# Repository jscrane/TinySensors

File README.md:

View this project on [CADLAB.io](https://cadlab.io/project/1612). 

TinySensors
===========
See [blog articles](http://programmablehardware.blogspot.ie/search/label/tinysensor).

* hub: lightweight Raspberry Pi server-side for TinySensor
* sensing: Database viewer
* eagle: TinySensor Eagle project

Software
========
* Arduino
  - IDE version [1.8.9](http://arduino.cc/en/Main/Software) or [uC-Makefile](https://github.com/jscrane/uC-Makefile)
  - [ATtiny core](https://github.com/SpenceKonde/ATTinyCore)
  - [nRF24](https://github.com/nRF24/RF24) library
  - [DHT22](https://github.com/jscrane/DHT22) library, slimmed-down for ATtiny

* Raspberry-Pi
  - Tested on Raspberry Pi 2, Pi 3 Model B and Pi Zero-W
  - [nRF24](https://github.com/nRF24/RF24) library
  - [BCM2835](http://www.airspayce.com/mikem/bcm2835) library
  - libmosquitto-dev
  - lcdproc

* Viewer
  - [Leiningen](http://leiningen.org) v2.0, or
  - [IntelliJ](http://www.jetbrains.com/idea) with the
[Cursive](https://cursiveclojure.com) plugin

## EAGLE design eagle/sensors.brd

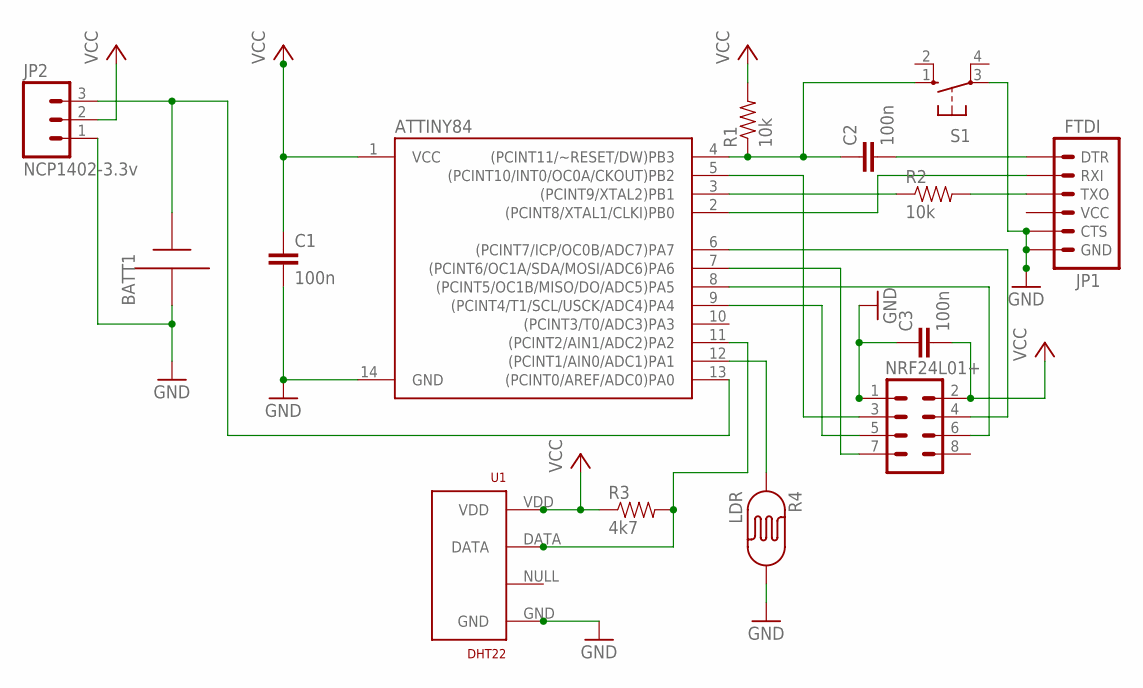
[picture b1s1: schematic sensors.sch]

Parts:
ATTINY84: ATTINY84ATTINY84-20PU; DIL14
BATT1: AAA; 12BH412
C1, C2, C3: 100n; CAP-PTH-5MM
JP1: FTDI; 1X06
JP2: NCP1402-3.3v; 1X03
NRF24L01+: M04X2; 2X4
R1, R2: 10k; AXIAL-0.3EZ
R3: 4k7; AXIAL-0.3EZ
R4: LDR; PHOTOCELL
S1: 10-XX; B3F-10XX
U1: DHT22; RHT03_DHT-22

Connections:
GND: ATTINY84.14 (GND), BATT1.-, C1.2, C3.1, JP1.5 (CTS), JP1.6 (GND), JP2.1, NRF24L01+.1, R4.2, S1.3, U1.GND
unnamed: ATTINY84.6 ((PCINT7/ICP/OC0B/ADC7)PA7), NRF24L01+.4
unnamed: ATTINY84.3 ((PCINT9/XTAL2)PB1), R2.P$1 (1)
unnamed: ATTINY84.4 ((PCINT11/~RESET/DW)PB3), C2.1, R1.P$1 (1), S1.1 (S)
unnamed: C2.2, JP1.1 (DTR)
unnamed: JP1.3 (TXO), R2.P$2 (2)
unnamed: ATTINY84.2 ((PCINT8/XTAL1/CLKI)PB0), JP1.2 (RXI)
unnamed: ATTINY84.7 ((PCINT6/OC1A/SDA/MOSI/ADC6)PA6), NRF24L01+.7
unnamed: ATTINY84.13 ((PCINT0/AREF/ADC0)PA0), BATT1.+, JP2.3
unnamed: ATTINY84.9 ((PCINT4/T1/SCL/USCK/ADC4)PA4), NRF24L01+.5
unnamed: ATTINY84.12 ((PCINT1/AIN0/ADC1)PA1), R4.1
unnamed: ATTINY84.11 ((PCINT2/AIN1/ADC2)PA2), R3.P$2 (2), U1.DATA
unnamed: ATTINY84.8 ((PCINT5/OC1B/MISO/DO/ADC5)PA5), NRF24L01+.6
unnamed: ATTINY84.5 ((PCINT10/INT0/OC0A/CKOUT)PB2), NRF24L01+.3
VCC: ATTINY84.1 (VCC), C1.1, C3.2, JP2.2, NRF24L01+.2, R1.P$2 (2), R3.P$1 (1), U1.VDD

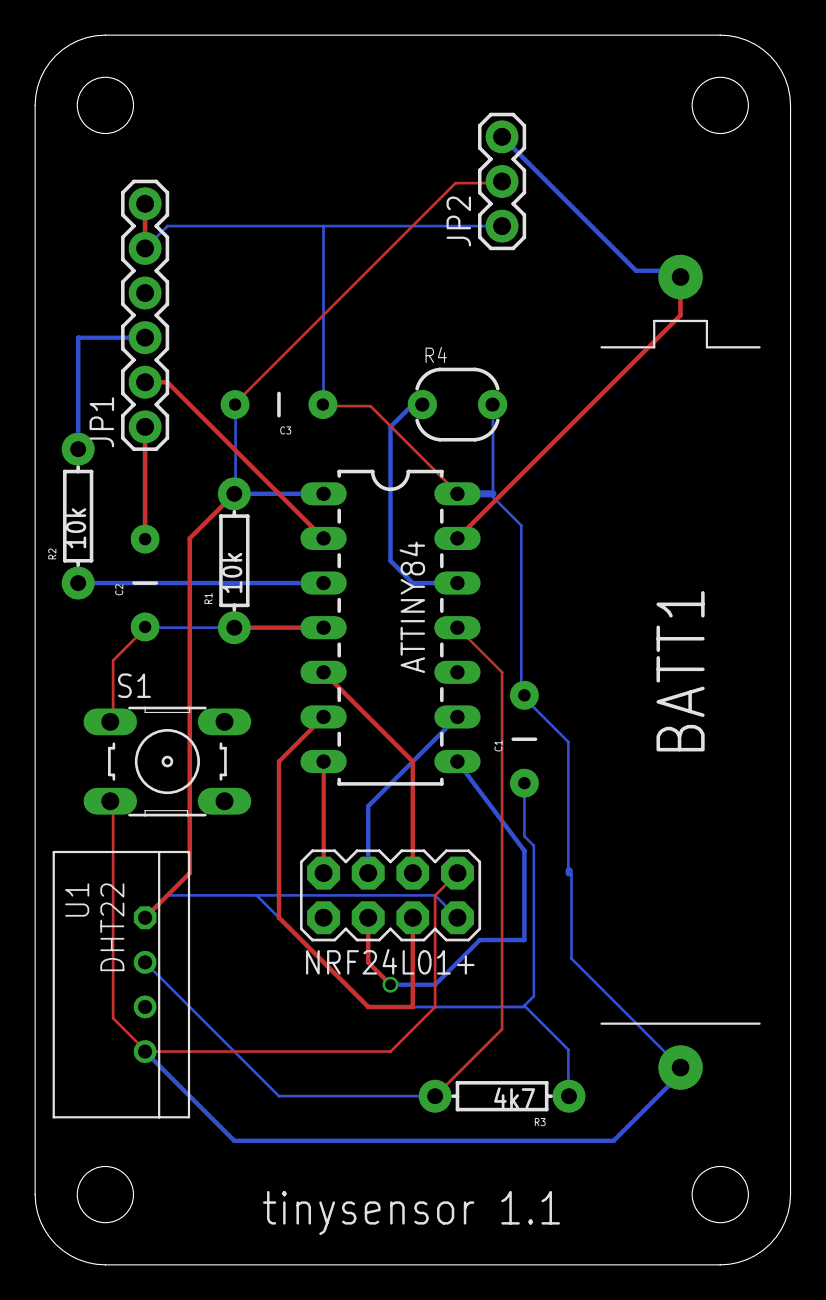
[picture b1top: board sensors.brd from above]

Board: 2 copper layers, 43.0 x 70.0 mm, 15 parts (0 on the bottom side), 15 nets.

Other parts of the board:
U$1: DP7043_V1

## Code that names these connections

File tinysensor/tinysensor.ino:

#include <avr/power.h>
#include <SPI.h>
#include <RF24.h>
#include <DHT.h>
#include <SoftwareSerial.h>

#include "tinysensor.h"
#include "wdt.h"

const uint8_t DHT_PIN = PIN_PA2;
const uint8_t CE_PIN = PIN_PB2, CS_PIN = PIN_PA7;
const uint8_t RX_PIN = PIN_PB1, TX_PIN = PIN_PB0;
const uint8_t LIGHT_PIN = A1, BATTERY_PIN = A0;

#if defined(DEBUG)
#pragma message "debugging"
SoftwareSerial serial(RX_PIN, TX_PIN);
#endif

RF24 radio(CE_PIN, CS_PIN);
DHT dht;

const uint8_t retry_count = 5;		// 250+5*15*250 = 19mS
const uint8_t retry_delay = 1;		// 1*250uS
const rf24_pa_dbm_e power = RF24_PA_LOW;

void setup(void)
{
	power_timer1_disable();

	dht.setup(DHT_PIN);

	pinMode(LIGHT_PIN, INPUT_PULLUP);

#if defined(DEBUG)
	serial.begin(TERMINAL_SPEED);
	serial.println(F("Time\tnRF\tDHT\tADC\tStatus\tHum\tTemp\tLight\tBattery\tSleep"));
#else
	pinMode(RX_PIN, INPUT_PULLUP);
	pinMode(TX_PIN, INPUT_PULLUP);
#endif

	SPI.begin();
	radio.begin();

	radio.setRetries(retry_delay, retry_count);
	radio.setDataRate(data_rate);
	radio.setCRCLength(crc_len);
	radio.setPALevel(power);
	radio.setChannel(channel);
	radio.setPayloadSize(sizeof(sensor_payload_t));
	radio.openWritingPipe(bridge_addr);
}

void loop(void)
{
	static uint32_t msgid;

	uint32_t start = micros();

	// power-up here to overlap with dht read
	radio.powerUp();

	unsigned lsens = analogRead(LIGHT_PIN);
	uint8_t batt = analogRead(BATTERY_PIN) / 4;
	uint8_t light = 255 - lsens / 4;

#if defined(ADAPTIVE)
	unsigned sleep = lsens / 4 + 1;
#else
	unsigned sleep = 300;
#endif

	uint8_t adcsra = ADCSRA;
	ADCSRA = 0;
	power_adc_disable();

	// millis() only counts time when the sketch is not sleeping
	uint32_t sd = micros();
	dht.resetTimer();
	int16_t h = dht.getHumidity();
	int16_t t = dht.getTemperature();
	uint8_t status = dht.getStatus();
	sensor_payload_t payload = { millis(), msgid++, h, t, NODE_ID, light, batt, status };

	uint32_t sr = micros();
	radio.stopListening();
	radio.write(&payload, sizeof(payload));
	radio.powerDown();

#if defined(DEBUG)
	uint32_t now = micros();
	serial.print(now - start);
	serial.print('\t');
	serial.print(now - sr);
	serial.print('\t');
	serial.print(sr - sd);
	serial.print('\t');
	serial.print(sd - start);
	serial.print('\t');
	serial.print(status);
	serial.print('\t');
	serial.print(h);
	serial.print('\t');
	serial.print(t);
	serial.print('\t');
	serial.print(light);
	serial.print('\t');
	serial.print(batt);
	serial.print('\t');
	serial.println(sleep);
#endif

	uint8_t prr = PRR;
	power_all_disable();

	wdt_sleep(sleep);

	PRR = prr;

	power_adc_enable();
	ADCSRA = adcsra;
}

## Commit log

2014-02-07 add Eagle files
2014-02-07 make capacitors bigger
2014-02-10 reorg
2014-02-10 compute proper rolling average filter outliers menus to select device and parameter
2014-02-11 - adding canned time periods - radio-buttons in menus
2014-02-11 - adding next and prev navigation
2014-02-11 - adding now function to reset position
2014-02-12 - split data from ui
2014-02-12 Subtree merged in tinysensor
2014-02-13 add deps
2014-02-13 update deps
2014-02-13 vary duty-cycle based on light
2014-02-13 weather script
2014-02-13 add timestamp field to weather
2014-02-13 - cleanups
2014-02-17 base duty-cycle on ambient light
2014-02-18 submodules
2014-02-18 banner
2014-02-19 be verbose correctly
2014-02-19 addresses are octal
2014-02-19 add remote socket interface
2014-02-20 add device type
2014-02-20 device_type_id
2014-02-20 pretty print to socket
2014-02-20 daemonize
2014-02-20 cleanup error handling
2014-02-20 adding node type
2014-02-20 re-added sensortest submodule
2014-02-20 break out payload
2014-02-20 using common header
2014-02-20 update README for submodules
2014-02-20 adding tinyrelay submodule
2014-02-20 - accelerators - zooming out
2014-02-20 - combining locations
2014-02-21 rearrange output
2014-02-21 - clean up queries
2014-02-21 - sort out workflow
2014-02-21 - break out charts into separate ns
2014-02-21 - remove unused fn
2014-02-23 schema update
2014-02-23 - schema update
2014-02-23 static data
2014-02-24 cleanup
2014-02-24 remove device_type_id from sensordata table
2014-02-24 collect existing network data
2014-02-25 adding device capabilities
2014-02-25 - using device_type to enable locations which possess a particular sensor
2014-02-26 light, features
2014-02-26 Makefile to dump schema
2014-02-27 Update TODO
2014-03-17 - add refresh
2014-03-25 - fix parameter order
2014-03-25 - time-windows now: [start-time, duration]
2014-03-27 - renaming db tables - adding support for multiple weather stations
2014-03-27 - DRY db auth - support multiple weather stations
2014-03-27 - renaming
2014-03-27 path
2014-03-27 - add misc namespace
2014-03-27 - bugfix
2014-04-25 firmware table
2014-04-25 add batteries table
2014-05-16 share auth with sensorhub
2014-05-16 bugfix
2014-05-16 add multiplexor
2014-05-28 - fix warnings
2014-07-09 fixing running under leiningen
2014-07-23 bugfixes
2014-07-27 fix -ve temps
2014-08-08 don't busy-wait if we have a client already
2014-08-08 gracefully exit on server death
2014-08-08 - adding watchdog support
2014-08-13 - x-axis label becomes start-date - busy-cursor for plot creation - update deps
2014-08-13 allow -ve temps
2015-02-06 add lcdproc mux client
2015-02-06 add update time
2015-02-06 use screen dims returned by server
2015-02-08 break out sensorlib
2015-02-08 cleanup sensorhub a bit add new fields to sensor_t
2015-02-08 plumb through more info from hub
2015-02-08 add mysqlmux mux client, remove functionality from sensorhub
2015-02-09 cache readings at mux and hand them out to new clients mux clients handle its failure properly now other bugfixes
2015-02-09 log to syslog
2015-02-09 software fix for hardware error
2015-02-10 improve fatal() and other cleanups
2015-02-10 add status lcd driver
2015-02-11 sensorhub uses same format as mux
2015-02-11 make sensor_t a class
2015-02-12 mux data from wireless and wired
2015-02-12 new wired sensors server script
2015-02-12 fix timeout
2015-02-12 schema changes
2015-02-12 mysql guy only writes fields appropriate for sensor
2015-02-13 lcd manages both sensor screens
2015-02-13 increase timeouts
2015-02-15 tweaks
2015-02-16 renumbering sensors
2015-02-26 add Makefile
2015-03-18 build with rf24's bcm library
2015-03-18 mux passes around sensor's short name
2015-03-18 rrd_graphs
2015-03-19 updating schema
2015-03-19 improve sensordb api
2015-03-19 more webby stuff
2015-03-20 more restiness
2015-03-22 better url handling
2015-03-26 dependencies
2015-03-27 mux attempts reconnect to failed upstream server, non-blocking bugfix daemon_mode
2015-07-03 initial connect from lcd is non-blocking
2015-07-03 index on time field
2015-07-03 some cleanups and updates
2015-07-03 todo
2015-07-03 some cleanups
2015-07-07 non-blocking connect for lcd + reconnect
2015-07-13 move on_connect() into sensorlib
2016-01-16 blank sensor not heard from recently
2016-12-13 disable rrd build
2016-12-13 configure sensor names from file
2016-12-13 add mqtt
2016-12-13 daemon mode fix
2017-01-04 support user/pass/root args
2017-01-05 connecting to opensensors.io
2017-01-07 mqtt+json
2017-06-30 add domoticz
2017-07-05 add raw flag
2017-10-09 remove jeelib
2017-10-10 board layout v1.1
2017-10-10 add script
2017-11-04 firmware
2018-04-06 startup script
2018-05-08 allow building some modules elsewhere so don't have to develop on rpi
2018-05-08 sleep while no LCDd
2018-05-08 display battery
2018-05-24 doc refresh
2018-05-24 better socket handling
2018-05-24 doc updates
2018-05-24 humidity
2018-05-25 cleanup socket handling
2018-05-26 label
2018-05-26 cleanups
2018-10-25 close lcd socket on write error
2018-10-25 LCDd location
2019-02-17 bugfox
2019-02-17 switch to git@ for submodules
2019-02-19 update for attiny core
2019-02-19 whitespace
2019-02-20 radio init; flash strings
2019-02-20 remove sensortest submodule
2019-02-20 remove tinysensor submodule
2019-02-20 remove tinyrelay
2019-02-21 code cleanup
2019-02-21 remove node-id in eeprom
2019-02-21 remove no-longer-needed binary files
2019-02-21 minor updates
2019-02-21 change retry interval (to save battery)
2019-02-21 Backlink to CADLAB.io has been added.
2019-03-11 switch to openweathermap
2019-03-15 scroller
2019-03-15 strict
2019-03-15 die if cannot read weather file
2019-03-16 rain
2019-03-16 tmin
2019-03-16 position date
2019-03-16 temp positioning
2019-03-17 centre description
2019-06-15 update to ATTinyCore
2019-06-15 update for ATTinyCore
2019-06-17 board definition for tinysensor
2019-06-17 fix for arduino ide
2019-06-20 rebuild for compatibility with ATTinyCore
2019-06-20 wdt_sleep
2019-06-21 code reorganisation + wdt_sleep
2019-06-21 reorganisation #2
2019-06-21 move constants into tinysensor.h
2019-06-21 change channel and data rate
2019-06-22 print details explicitly
2019-06-22 call out defaults for power and crc_len
2019-06-22 setCRCLength
2019-06-26 timing
2019-06-26 optimise payload
2019-08-08 non-blocking init_addr()
2019-09-03 alarm
2019-09-10 fork child process to handle rf24; restart it when it hangs
2019-11-11 change server
2019-11-11 don't pad day with space
2019-11-11 scroller width
2020-01-31 esp8266 bridge
2020-02-01 add configs for nRF24L01+ radio
2020-02-02 node_id config
2020-02-21 update for v1.3.3 core
2020-03-09 LTO flags
2020-03-09 test with nRF24
2020-05-08 rf24bridge + sensor w/o RF24Network
2020-05-08 update hub
2020-05-15 working sensorhub + fix compiler warnings
2020-05-15 rewire board
2020-05-15 minor fixes
2020-05-16 add test node
2020-05-16 warning
2020-05-16 change channel to 110
2020-05-16 use RF24-rpi for now
2020-05-16 add Test Sensor to Domoticz
2020-05-17 power bugfix
2020-05-19 cleanup makefile
2020-05-20 fix #5
2020-05-20 remove sensortest + rename sketches -> tinysensor
2020-05-27 rename sensor
2020-05-29 wemo
2020-05-29 install to /usr/local
2020-05-30 add systemd units for rfcomm and lcdd
2020-06-15 add node
2020-07-06 units on screen
2020-07-09 place unit beside last-updated sensor
2020-07-11 tiny fixes
2020-08-17 update core version
2020-08-17 disable adc before sleeping
2020-09-04 use port-pins
2020-09-07 add client ids
2020-09-09 more power-saving: disable usi and timer1, turn off light pullup except when read
2020-09-16 add infrastructure for 1MHz, #13
2020-09-25 json keys must be double-quotes
2020-09-25 add node-id to json message
2020-09-26 remove dup
2020-09-26 rough initial cut of mqtt graphing sketch
2020-09-29 4-bit colour depth for sprites
2020-09-30 add graph_config
2020-10-01 add Graph class
2020-10-02 multiple graphs
2020-10-02 add graph title
2020-10-02 more graphs + display limits
2020-10-02 display legend
2020-10-03 configure graphs
2020-10-03 add config
2020-10-03 expose status timeout as optional cmd-line arg
2020-10-03 expose lcd timeout
2020-10-04 remove smoother
2020-10-04 remove debug flag from config
2020-10-10 add node_time to mqtt messages
2020-10-10 tracking RF24 library changes
2020-10-12 add msg_id
2020-10-14 add init target
2020-11-15 cleanup wdt_sleep(); save 5ms in main loop
2020-11-23 disable all devices before wdt
2020-12-15 new nRF24 library
2021-01-11 add average wake time
2021-02-07 tiny bugfix
2021-03-18 add upload.maximum for tinysensor
2021-04-30 battery stats
2021-09-15 5 min sleep
2021-09-23 bugfix mqtt
2021-10-01 'host not found' can be transient error if it's rebooting
2021-10-01 handle NO_ADDRESS response to gethostbyname()
2022-08-09 lcdproc owm client
2022-08-10 remove sheeva from mux. remove wired sensors from nodes.txt.
2022-08-10 add toggles to enable/disable wireless/wired sensor display for lcd
2023-11-10 update to crc16
2023-11-10 battery
2023-11-10 Wireless (#17)
    * remove sheeva from mux. remove wired sensors from nodes.txt.
    * add toggles to enable/disable wireless/wired sensor display for lcd
    * update to crc16
2023-11-10 Wireless (#18)
    * remove sheeva from mux. remove wired sensors from nodes.txt.
    * add toggles to enable/disable wireless/wired sensor display for lcd
    * update to crc16
    * battery
2026-05-11 update menu name

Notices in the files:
parts and their libraries:
SparkFun-DigitalIC: Licensing: CC v3.0 Share-Alike You are welcome to use this library for commercial purposes.
